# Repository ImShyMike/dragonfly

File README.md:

# dragonfly

A tiny 3.5" FPV drone for [highway](https://highway.hackclub.com) with a fully custom frame, corners, softmounts and ELRS receiver.

I've seen many FPV videos and always thought that it was really cool. Only issue is that I only own a small toy drone without a camera.

When highway released I thought it would be a great oportunity to learn what goes into designing your own FPV drone. After alot of research I managed to make a decent looking frame and find parts that could keep the cost reasonably low.

---

## Render

<sub>The model with sample props, motors and camera (along with a 15cm ruler for scale).</sub>

---

## BOM

| Part                                     | Qty | Price (USD) | Link                                                                                                                                   |
| ---------------------------------------- | :-: | :---------: | -------------------------------------------------------------------------------------------------------------------------------------- |
| SpeedyBee F405 Mini BLS 35A 20×20 Stack  |  1  |       60.00 | [https://www.speedybee.com/speedybee-f405-mini-bls-35a-20x20-stack](https://www.speedybee.com/speedybee-f405-mini-bls-35a-20x20-stack) |
| 20 mm Aluminum Standoffs (pack)          |  1  |        1.86 | [https://pt.aliexpress.com/item/1005007945167923.html](https://pt.aliexpress.com/item/1005007945167923.html)                           |
| HQProp 3525 Prop Set                     |  1  |        3.31 | [https://pt.aliexpress.com/item/1005008744409414.html](https://pt.aliexpress.com/item/1005008744409414.html)                           |
| CADDX ANT Camera                         |  1  |       13.98 | [https://pt.aliexpress.com/item/1005006086694992.html](https://pt.aliexpress.com/item/1005006086694992.html)                           |
| Omnidirectional Antenna Pair             |  1  |        2.46 | [https://pt.aliexpress.com/item/1005007126266614.html](https://pt.aliexpress.com/item/1005007126266614.html)                           |
| YSIDO 1505 2650KV Brushless Motor Set    |  1  |       29.11 | [https://pt.aliexpress.com/item/1005007544080274.html](https://pt.aliexpress.com/item/1005007544080274.html)                           |
| HGLRC Zeus Nano VTX                      |  1  |       22.96 | [https://pt.aliexpress.com/item/1005008043478143.html](https://pt.aliexpress.com/item/1005008043478143.html)                           |
| Mini RHCP 5.8 GHz Lollipop Antenna (UFL) |  1  |        5.34 | [https://pt.aliexpress.com/item/4001365632031.html](https://pt.aliexpress.com/item/4001365632031.html)                                 |
| **Total**                                |     |  **139.02** |                                                                                                                                        |

The current price of the ELRS receiver is 69.60$ and using the cheapest shipping the total is at 215.91$.

The BOM does not account for the frame and battery as I couldn't get that under 150$ D:

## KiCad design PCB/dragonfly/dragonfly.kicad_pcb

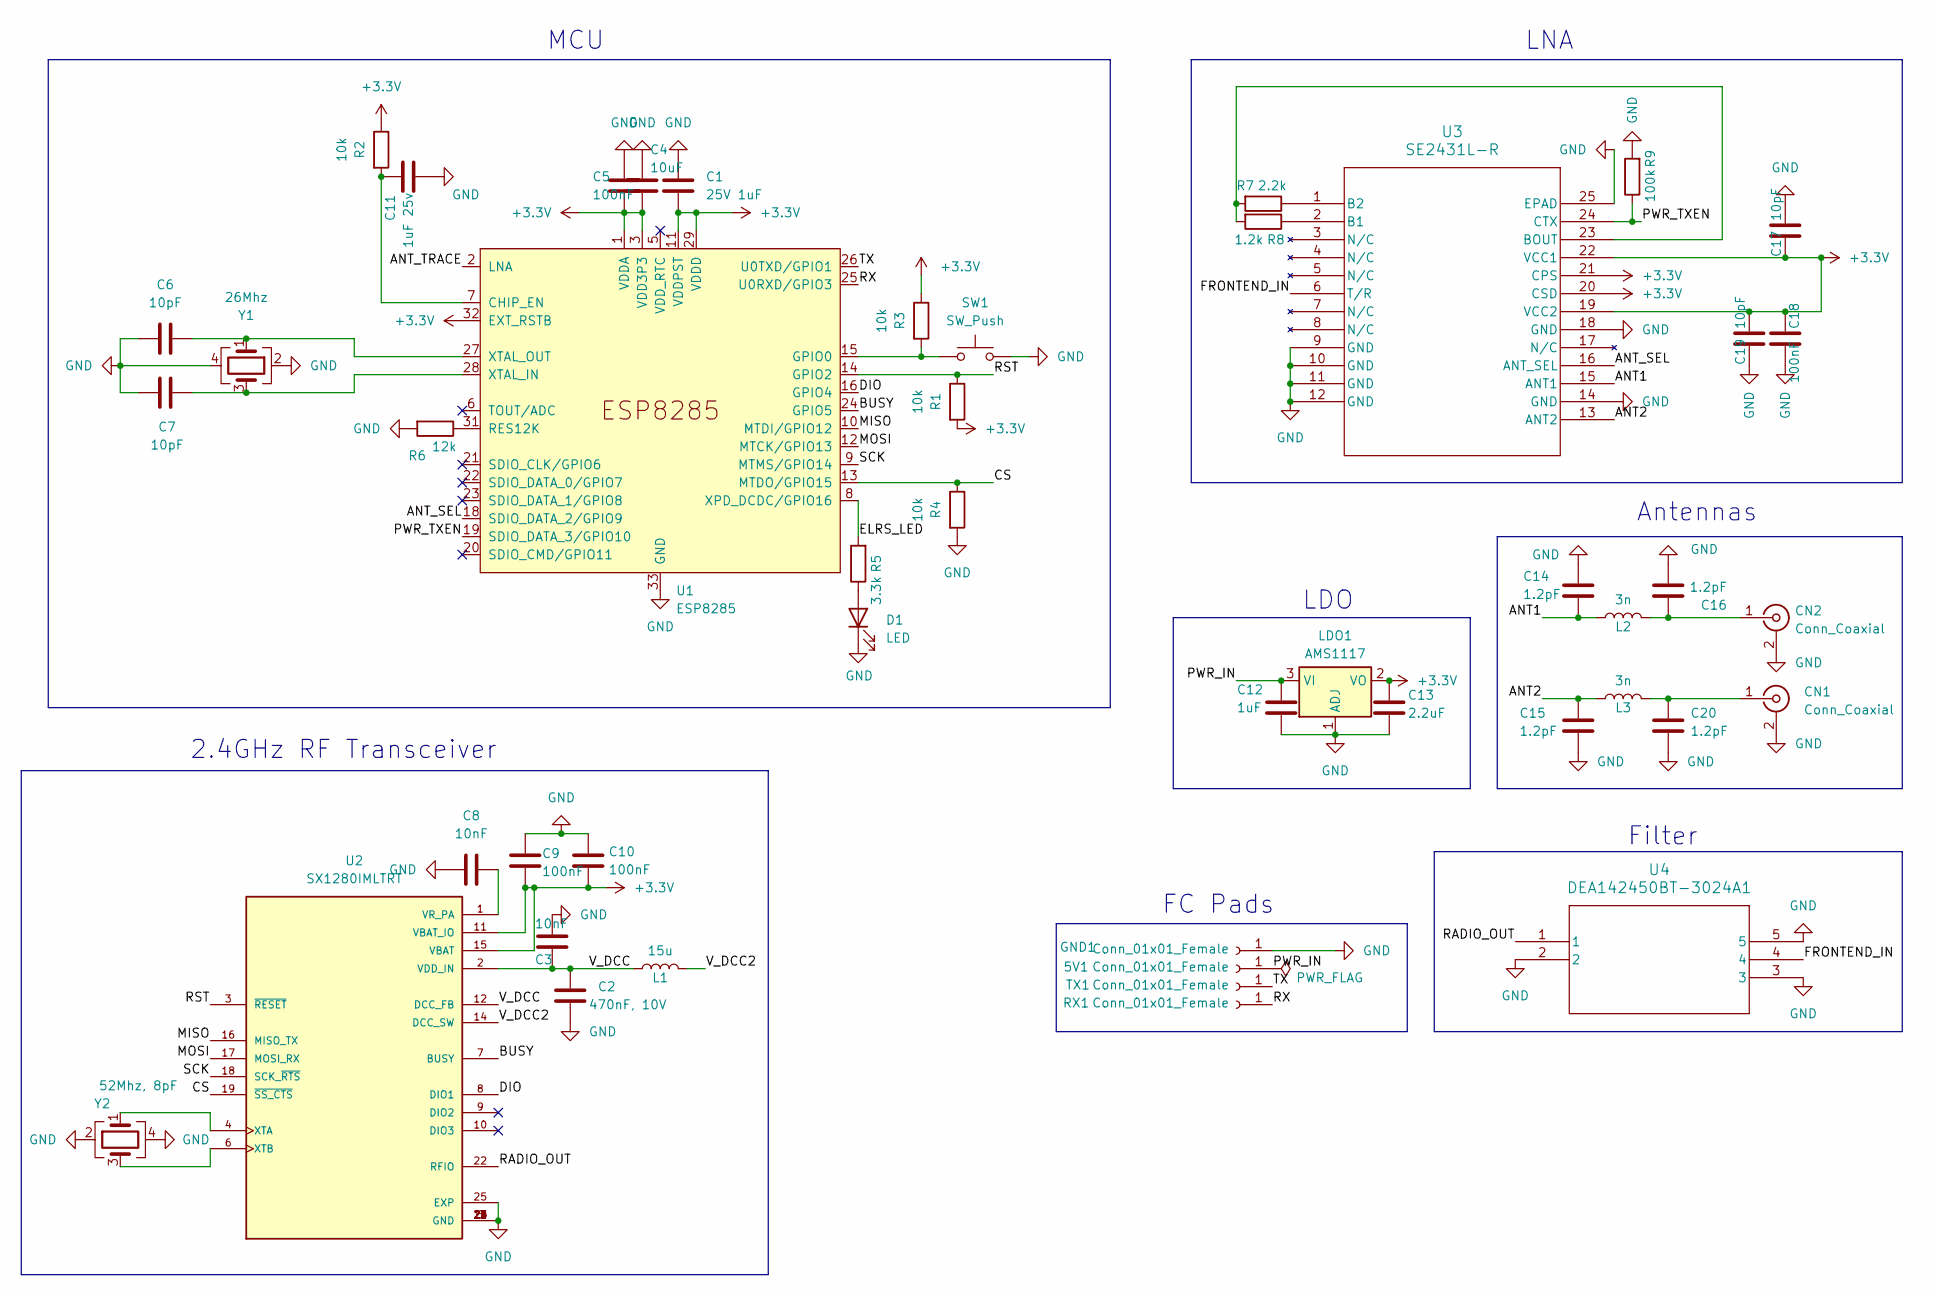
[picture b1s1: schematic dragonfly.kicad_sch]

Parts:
5V1: Conn_01x01_Female; TestPoint_Pad_2.5x2.5mm
C1: 25V 1uF; C_0402_1005Metric
C2: 470nF, 10V; C_0402_1005Metric; LCSC C47339
C3: 10nF; C_0402_1005Metric; LCSC C15195
C4: 10uF; C_0402_1005Metric
C5, C9, C10: 100nF; C_0402_1005Metric
C6, C7: 10pF; C_0402_1005Metric
C8: 10nF; C_0402_1005Metric
C11: 1uF 25v; C_0402_1005Metric; LCSC C52923
C12: 1uF; C_0402_1005Metric; LCSC C52923
C13: 2.2uF; C_0402_1005Metric; LCSC C52923
C14, C15, C16, C20: 1.2pF; C_0402_1005Metric; LCSC C327292
C17, C19: 10pF; C_0402_1005Metric; LCSC C32949
C18: 100nF; C_0402_1005Metric; LCSC C1525
CN1, CN2: Conn_Coaxial; U.FL_Hirose_U.FL-R-SMT-1_Vertical; Part Hirose U.FL-R-SMT-1(80); LCSC C88374
D1: LED; LED_0603_1608Metric; LCSC C2286
GND1: Conn_01x01_Female; TestPoint_Pad_2.5x2.5mm
L1: 15u; L_0805_2012Metric; LCSC C486333
L2, L3: 3n; L_0402_1005Metric; LCSC C269824
LDO1: AMS1117; SOT-223-3_TabPin2
R1, R2, R3, R4: 10k; R_0402_1005Metric
R5: 3.3k; R_0402_1005Metric; LCSC C25890
R6: 12k; R_0402_1005Metric; LCSC C25752
R7: 2.2k; R_0402_1005Metric; LCSC C25879
R8: 1.2k; R_0402_1005Metric; LCSC C25862
R9: 100k; R_0402_1005Metric; LCSC C25741
RX1: Conn_01x01_Female; TestPoint_Pad_2.5x2.5mm
SW1: SW_Push; SW_SPST_B3U-1000P-B
TX1: Conn_01x01_Female; TestPoint_Pad_2.5x2.5mm
U1: ESP8285; QFN-32-1EP_5x5mm_P0.5mm_EP3.45x3.45mm
U2: SX1280IMLTRT; XCVR_SX1280IMLTRT; PARTREV 3.3
U3: SE2431L-R; SE2431L_SKY
U4: DEA142450BT-3024A1; RF_3024A1_TDK
Y1: 26Mhz; Crystal_SMD_2016-4Pin_2.0x1.6mm
Y2: 52Mhz, 8pF; Crystal_SMD_2016-4Pin_2.0x1.6mm; LCSC C781783

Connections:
+3.3V: C1.2, C4.2, C5.1, C9.1, C10.1, C13.1, C17.2, C18.1, C19.1, LDO1.2 (VO), R1.2, R2.1, R3.1, U1.1 (VDDA), U1.3 (VDD3P3), U1.4 (VDD3P3), U1.11 (VDDPST), U1.17 (VDDPST), U1.29 (VDDD), U1.30 (VDDA), U1.32 (EXT_RSTB), U2.11 (VBAT_IO), U2.15 (VBAT), U3.19 (VCC2), U3.20 (CSD), U3.21 (CPS), U3.22 (VCC1)
/ANT1: C14.2, L2.1, U3.15 (ANT1)
/ANT2: C15.1, L3.1, U3.13 (ANT2)
/ANT_SEL: U1.18 (SDIO_DATA_2/GPIO9), U3.16 (ANT_SEL)
/ANT_TRACE: U1.2 (LNA)
/BUSY: U1.24 (GPIO5), U2.7 (BUSY)
/CS: R4.1, U1.13 (MTDO/GPIO15), U2.19 (~SS_CTS)
/DIO: U1.16 (GPIO4), U2.8 (DIO1)
/ELRS_LED: R5.2, U1.8 (XPD_DCDC/GPIO16)
/FRONTEND_IN: U3.6 (T/R), U4.4
/MISO: U1.10 (MTDI/GPIO12), U2.16 (MISO_TX)
/MOSI: U1.12 (MTCK/GPIO13), U2.17 (MOSI_RX)
/PWR_IN: 5V1.1, C12.1, LDO1.3 (VI)
/PWR_TXEN: R9.1, U1.19 (SDIO_DATA_3/GPIO10), U3.24 (CTX)
/RADIO_OUT: U2.22 (RFIO), U4.1
/RST: R1.1, U1.14 (GPIO2), U2.3 (~RESET)
/RX: RX1.1, U1.25 (U0RXD/GPIO3)
/SCK: U1.9 (MTMS/GPIO14), U2.18 (SCK_~RTS)
/TX: TX1.1, U1.26 (U0TXD/GPIO1)
/V_DCC: C2.1, C3.2, L1.1, U2.2 (VDD_IN), U2.12 (DCC_FB)
/V_DCC2: L1.2, U2.14 (DCC_SW)
GND: C1.1, C2.2, C3.1, C4.1, C5.2, C6.1, C7.1, C8.1, C9.2, C10.2, C11.2, C12.2, C13.2, C14.1, C15.2, C16.2, C17.1, C18.2, C19.2, C20.2, CN1.2 (Ext), CN2.2 (Ext), D1.1 (K), GND1.1, LDO1.1 (ADJ), R4.2, R6.2, R9.2, SW1.2, U1.33 (GND), U2.5 (GND), U2.13 (GND), U2.20 (GND), U2.21 (GND), U2.23 (GND), U2.24 (GND), U2.25 (EXP), U3.9 (GND), U3.10 (GND), U3.11 (GND), U3.12 (GND), U3.14 (GND), U3.18 (GND), U3.25 (EPAD), U4.2, U4.3, U4.5, Y1.2, Y1.4, Y2.2, Y2.4
unnamed: C20.1, CN1.1 (In), L3.2
unnamed: C16.1, CN2.1 (In), L2.2
unnamed: D1.2 (A), R5.1
unnamed: C11.1, R2.2, U1.7 (CHIP_EN)
unnamed: R3.2, SW1.1, U1.15 (GPIO0)
unnamed: R6.1, U1.31 (RES12K)
unnamed: C7.2, U1.28 (XTAL_IN), Y1.3
unnamed: C6.2, U1.27 (XTAL_OUT), Y1.1
unnamed: C8.2, U2.1 (VR_PA)
unnamed: U2.4 (XTA), Y2.1
unnamed: U2.6 (XTB), Y2.3
unnamed: R8.1, U3.2 (B1)
unnamed: R7.1, U3.1 (B2)
unnamed: R7.2, R8.2, U3.23 (BOUT)

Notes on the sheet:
Antennas
LNA
2.4GHz RF Transceiver
FC Pads
LDO
MCU
Filter

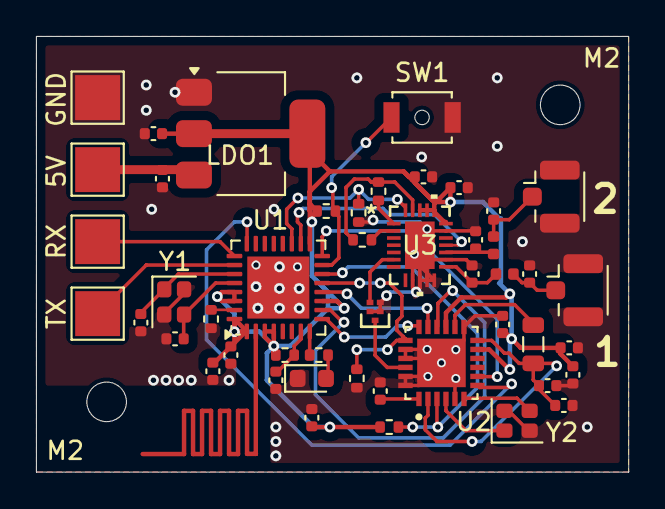
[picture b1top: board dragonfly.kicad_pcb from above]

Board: 2 copper layers, 32.9 x 24.2 mm, 49 parts (0 on the bottom side), 35 nets.

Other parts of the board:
M2, M2#2: MountingHole_2.2mm_M2

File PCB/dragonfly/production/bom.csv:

Designator,Footprint,Quantity,Value,LCSC Part #
"5V1, GND1, RX1, TX1",TestPoint_Pad_2.5x2.5mm,4,Conn_01x01_Female,
C1,0402,1,25V 1uF,
"C10, C5, C9",0402,3,100nF,
C11,0402,1,1uF 25v,C52923
C12,0402,1,1uF,C52923
C13,0402,1,2.2uF,C52923
"C14, C15, C16, C20",0402,4,1.2pF,C327292
"C17, C19",0402,2,10pF,C32949
C18,0402,1,100nF,C1525
C2,0402,1,"470nF, 10V",C47339
C3,0402,1,10nF,C15195
C4,0402,1,10uF,
"C6, C7",0402,2,10pF,
C8,0402,1,10nF,
"CN1, CN2",U.FL_Hirose_U.FL-R-SMT-1_Vertical,2,Conn_Coaxial,C88374
D1,0603,1,LED,C2286
L1,0805,1,15u,C486333
"L2, L3",0402,2,3n,C269824
LDO1,SOT-223-3_TabPin2,1,AMS1117,
"R1, R2, R3, R4",0402,4,10k,
R5,0402,1,3.3k,C25890
R6,0402,1,12k,C25752
R7,0402,1,2.2k,C25879
R8,0402,1,1.2k,C25862
R9,0402,1,100k,C25741
SW1,SW_SPST_B3U-1000P-B,1,SW_Push,
U1,QFN-32-1EP_5x5mm_P0.5mm_EP3.45x3.45mm,1,ESP8285,
U2,XCVR_SX1280IMLTRT,1,SX1280IMLTRT,
U3,SE2431L_SKY,1,SE2431L-R,
U4,RF_3024A1_TDK,1,DEA142450BT-3024A1,
Y1,Crystal_SMD_2016-4Pin_2.0x1.6mm,1,26Mhz,
Y2,Crystal_SMD_2016-4Pin_2.0x1.6mm,1,"52Mhz, 8pF",C781783

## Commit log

2025-06-14 update :D
2025-06-14 forgot time
2025-06-15 im going to sleep now
2025-06-17 BOM :yay:
2025-06-17 another update :D
2025-06-17 README update
2025-06-17 add CAD
2025-06-20 IT'S UNDER 150$!!!!
2025-06-20 typo
2025-06-20 oopsies
2025-06-24 custom ELRS receiver :3
2025-06-24 JLCPCB BOM
2025-06-24 update total hours
